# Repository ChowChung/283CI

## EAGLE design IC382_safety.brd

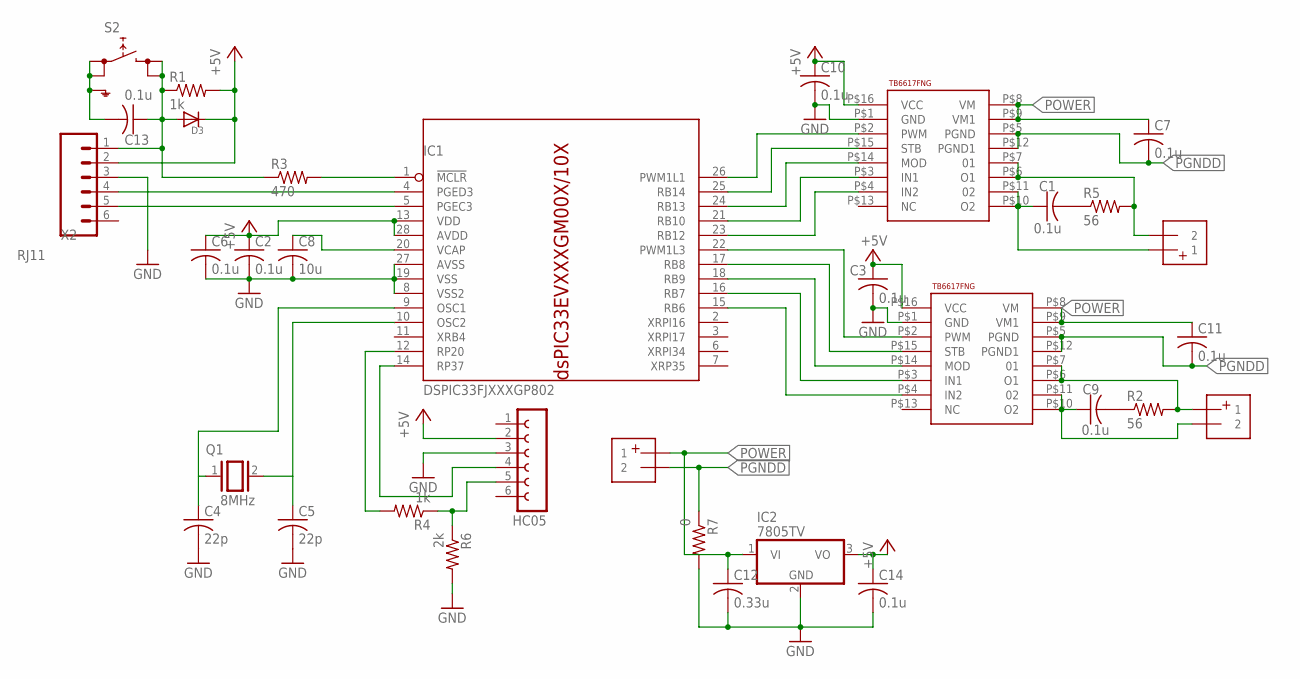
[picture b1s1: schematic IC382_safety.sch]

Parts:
C1, C2, C3, C6, C7, C9, C10, C11, C13, C14: 0.1u; C0805
C4, C5: 22p; C0805
C8: 10u; C0805
C12: 0.33u; C0805
D3: DIODESOD-123; SOD-123
DRIVER1, DRIVER2: SSOP16
HC05: FE06-1; FE06
IC1: DSPIC33FJXXXGP802; SO28W
IC2: 7805TV; TO220V
J1, J2: 1X2-3.5MM
POWERSUPPLY: 1X2-3.5MM
Q1: 8MHz; QS
R1, R4: 1k; M0805
R2, R5: 56; M0805
R3: 470; M0805
R6: 2k; M0805
R7: 0; M0805
S2: SKHMPWE010; SKHMPXE010
X2: RJ11; RJ11-6

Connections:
+5V: C2.1, C3.1, C6.1, C10.1, C14.1, D3.C, DRIVER1.P$16 (VCC), DRIVER2.P$16 (VCC), HC05.2, IC1.13 (VDD), IC1.28 (AVDD), IC2.3 (VO), R1.2, X2.2
GND: C2.2, C3.2, C4.2, C5.2, C6.2, C8.2, C10.2, C12.2, C14.2, DRIVER1.P$1 (GND), DRIVER2.P$1 (GND), HC05.3, IC1.8 (VSS2), IC1.19 (VSS), IC1.27 (AVSS), IC2.2 (GND), R6.2, R7.2, X2.3
M-2: DRIVER1.P$6 (O1), DRIVER1.P$7 (01), J1.2, R5.2
unnamed: HC05.4, IC1.14 (RP37)
unnamed: C5.1, IC1.10 (OSC2), Q1.2
unnamed: IC1.4 (PGED3), X2.4
unnamed: DRIVER2.P$4 (IN2), IC1.15 (RB6)
unnamed: C8.1, IC1.20 (VCAP)
unnamed: C13.1, D3.A, R1.1, R3.1, S2.3 (2.1), S2.4 (2.2), X2.1
unnamed: DRIVER2.P$2 (PWM), IC1.22 (PWM1L3)
unnamed: IC1.1 (!MCLR), R3.2
unnamed: IC1.5 (PGEC3), X2.5
unnamed: C4.1, IC1.9 (OSC1), Q1.1
unnamed: IC1.12 (RP20), R4.2
unnamed: DRIVER1.P$2 (PWM), IC1.26 (PWM1L1)
unnamed: DRIVER1.P$15 (STB), IC1.25 (RB14)
unnamed: DRIVER1.P$14 (MOD), IC1.24 (RB13)
unnamed: DRIVER1.P$3 (IN1), IC1.21 (RB10)
unnamed: DRIVER1.P$4 (IN2), IC1.23 (RB12)
unnamed: DRIVER2.P$15 (STB), IC1.17 (RB8)
unnamed: C1.1, DRIVER1.P$10 (O2), DRIVER1.P$11 (02), J1.1
unnamed: DRIVER2.P$14 (MOD), IC1.18 (RB9)
unnamed: C1.2, R5.1
unnamed: DRIVER2.P$3 (IN1), IC1.16 (RB7)
unnamed: HC05.5, R4.1, R6.1
unnamed: C13.2, S2.1 (1.1), S2.2 (1.2), S2.5 (SH)
unnamed: DRIVER2.P$6 (O1), DRIVER2.P$7 (01), J2.1, R2.2
unnamed: C9.1, DRIVER2.P$10 (O2), DRIVER2.P$11 (02), J2.2
unnamed: C9.2, R2.1
PGNDD: C7.2, C11.2, DRIVER1.P$5 (PGND), DRIVER1.P$12 (PGND1), DRIVER2.P$5 (PGND), DRIVER2.P$12 (PGND1), POWERSUPPLY.2, R7.1
POWER: C7.1, C11.1, C12.1, DRIVER1.P$8 (VM), DRIVER1.P$9 (VM1), DRIVER2.P$8 (VM), DRIVER2.P$9 (VM1), IC2.1 (VI), POWERSUPPLY.1

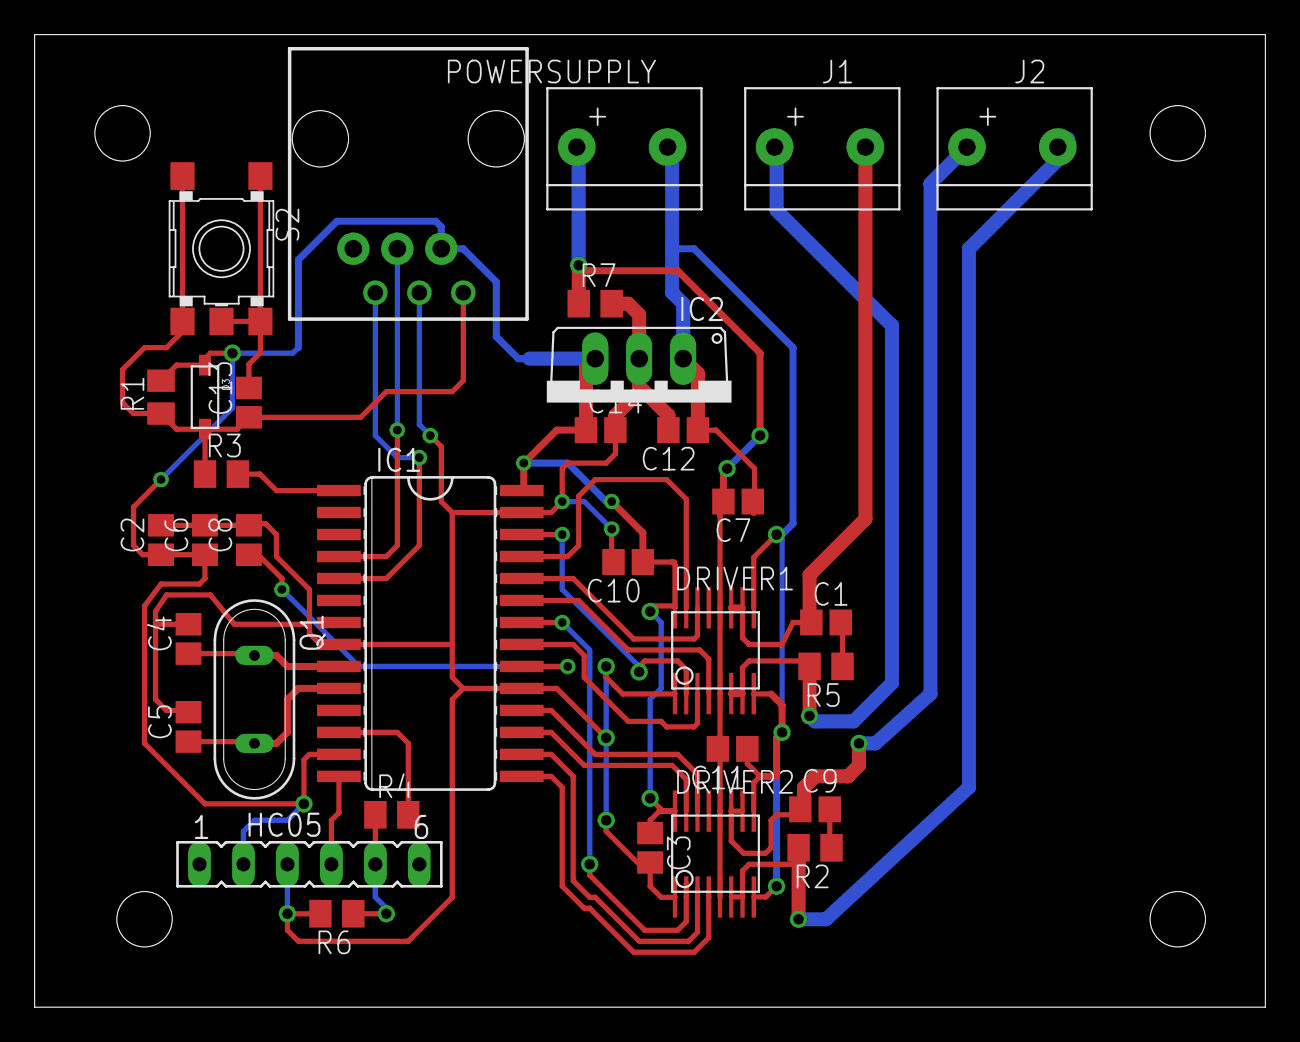
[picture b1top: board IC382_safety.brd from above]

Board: 2 copper layers, 71.1 x 56.2 mm, 33 parts (0 on the bottom side), 31 nets.

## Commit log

2017-02-03 Schematic and layout
2017-02-03 Hm10
    Ble hm10 test code

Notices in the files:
parts and their libraries:
SparkFun-Connectors: Licensing: Creative Commons ShareAlike 4.0 International - https://creativecommons.org/licenses/by-sa/4.0
